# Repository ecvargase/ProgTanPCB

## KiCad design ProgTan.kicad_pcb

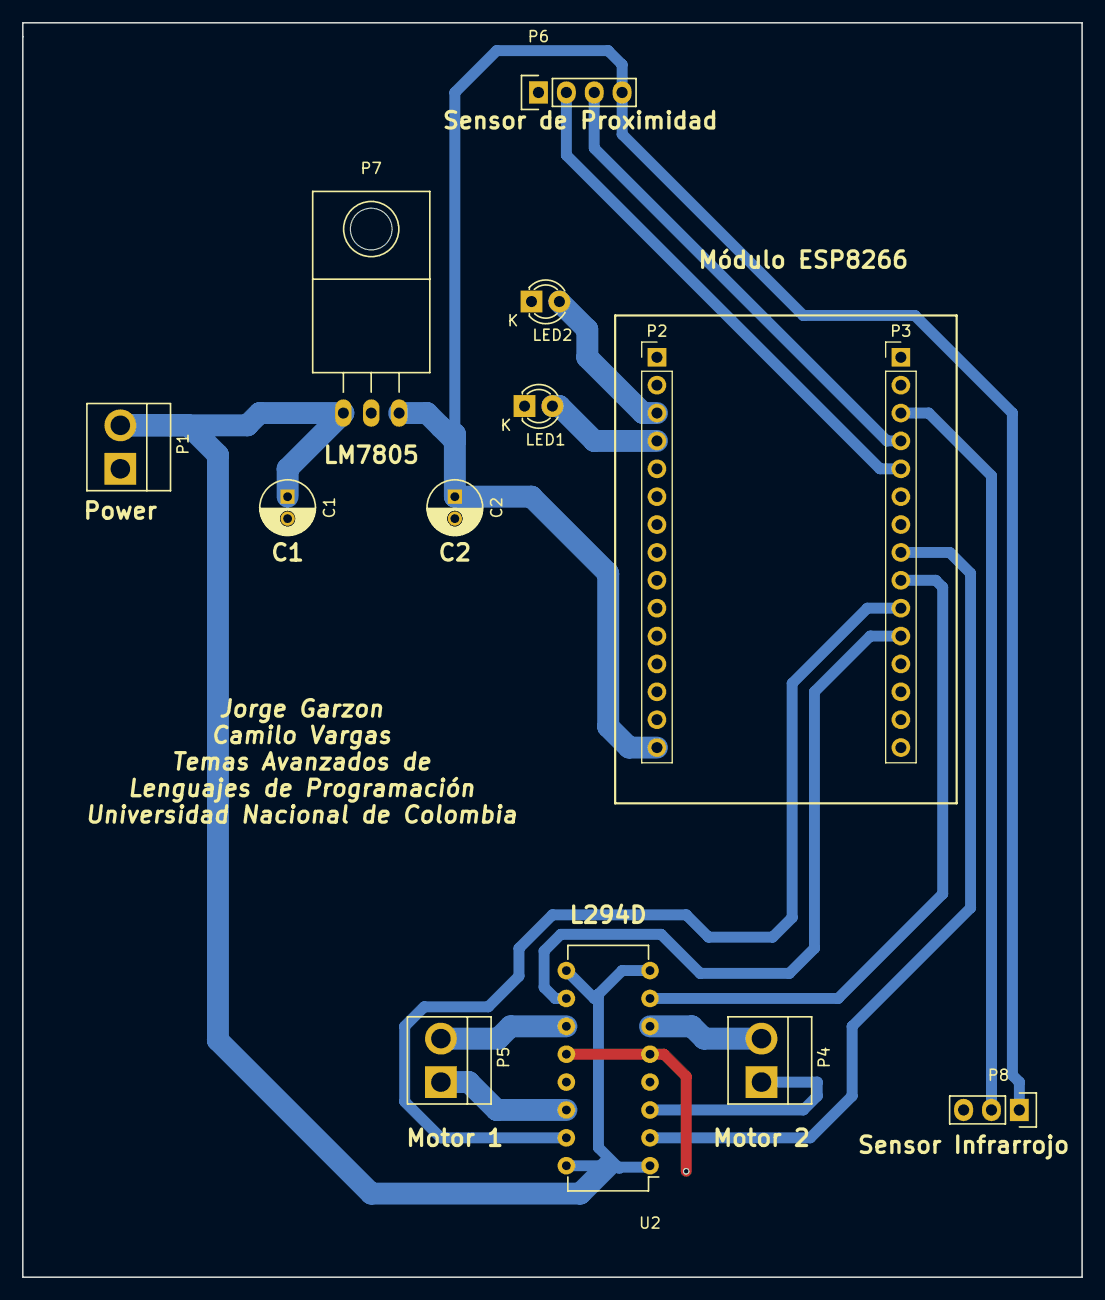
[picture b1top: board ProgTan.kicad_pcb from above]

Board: 2 copper layers, 96.5 x 114.3 mm, 13 parts (0 on the bottom side), 16 nets.

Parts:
C1, C2: C; C_Radial_D5_L11_P2
LED1, LED2: LED; LED-3MM
P1: Power; Pin_Header_Straight_1x02_Pitch3.96mm_Friction_Lock
P2: ESP_A; Pin_Header_Straight_1x15_Pitch2.54mm
P3: ESP_B; Pin_Header_Straight_1x15_Pitch2.54mm
P4: MOTOR2; Pin_Header_Straight_1x02_Pitch3.96mm_Friction_Lock
P5: MOTOR1; Pin_Header_Straight_1x02_Pitch3.96mm_Friction_Lock
P6: Sensor Proximidad; Socket_Strip_Straight_1x04
P7: LM7805; TO-220_Neutral123_Horizontal
P8: Sensor Infrarrojo; Socket_Strip_Straight_1x03
U2: L294D; DIP-16_W7.62mm

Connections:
/GPI00: P3.4, P6.3
/GPI02: P3.5, P6.2
/GPI04: P3.3, P8.2
/GPI09: LED1.2, P2.4
/GPI10: LED2.2, P2.3
/GPI12: P3.9, U2.7
/GPI13: P3.10, U2.15
/GPI14: P3.8, U2.2
/GPI15: P3.11, U2.10
/M1_1: P4.1, U2.3
/M1_2: P4.2, U2.6
/M2_1: P5.1, U2.14
/M2_2: P5.2, U2.11
/Vin: C1.1, P1.2, P7.1, U2.1, U2.8, U2.9, U2.16
/Vo: C2.1, P2.15, P6.4, P7.3, P8.1
GND: C1.2, C2.2, LED1.1, LED2.1, P1.1, P2.10, P2.14, P3.7, P3.14, P6.1, P7.2, P8.3, U2.4, U2.5, U2.12, U2.13

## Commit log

2018-03-24 Add images
2018-03-24 Modificación en las rutas de tierra
2018-05-25 General fixes
